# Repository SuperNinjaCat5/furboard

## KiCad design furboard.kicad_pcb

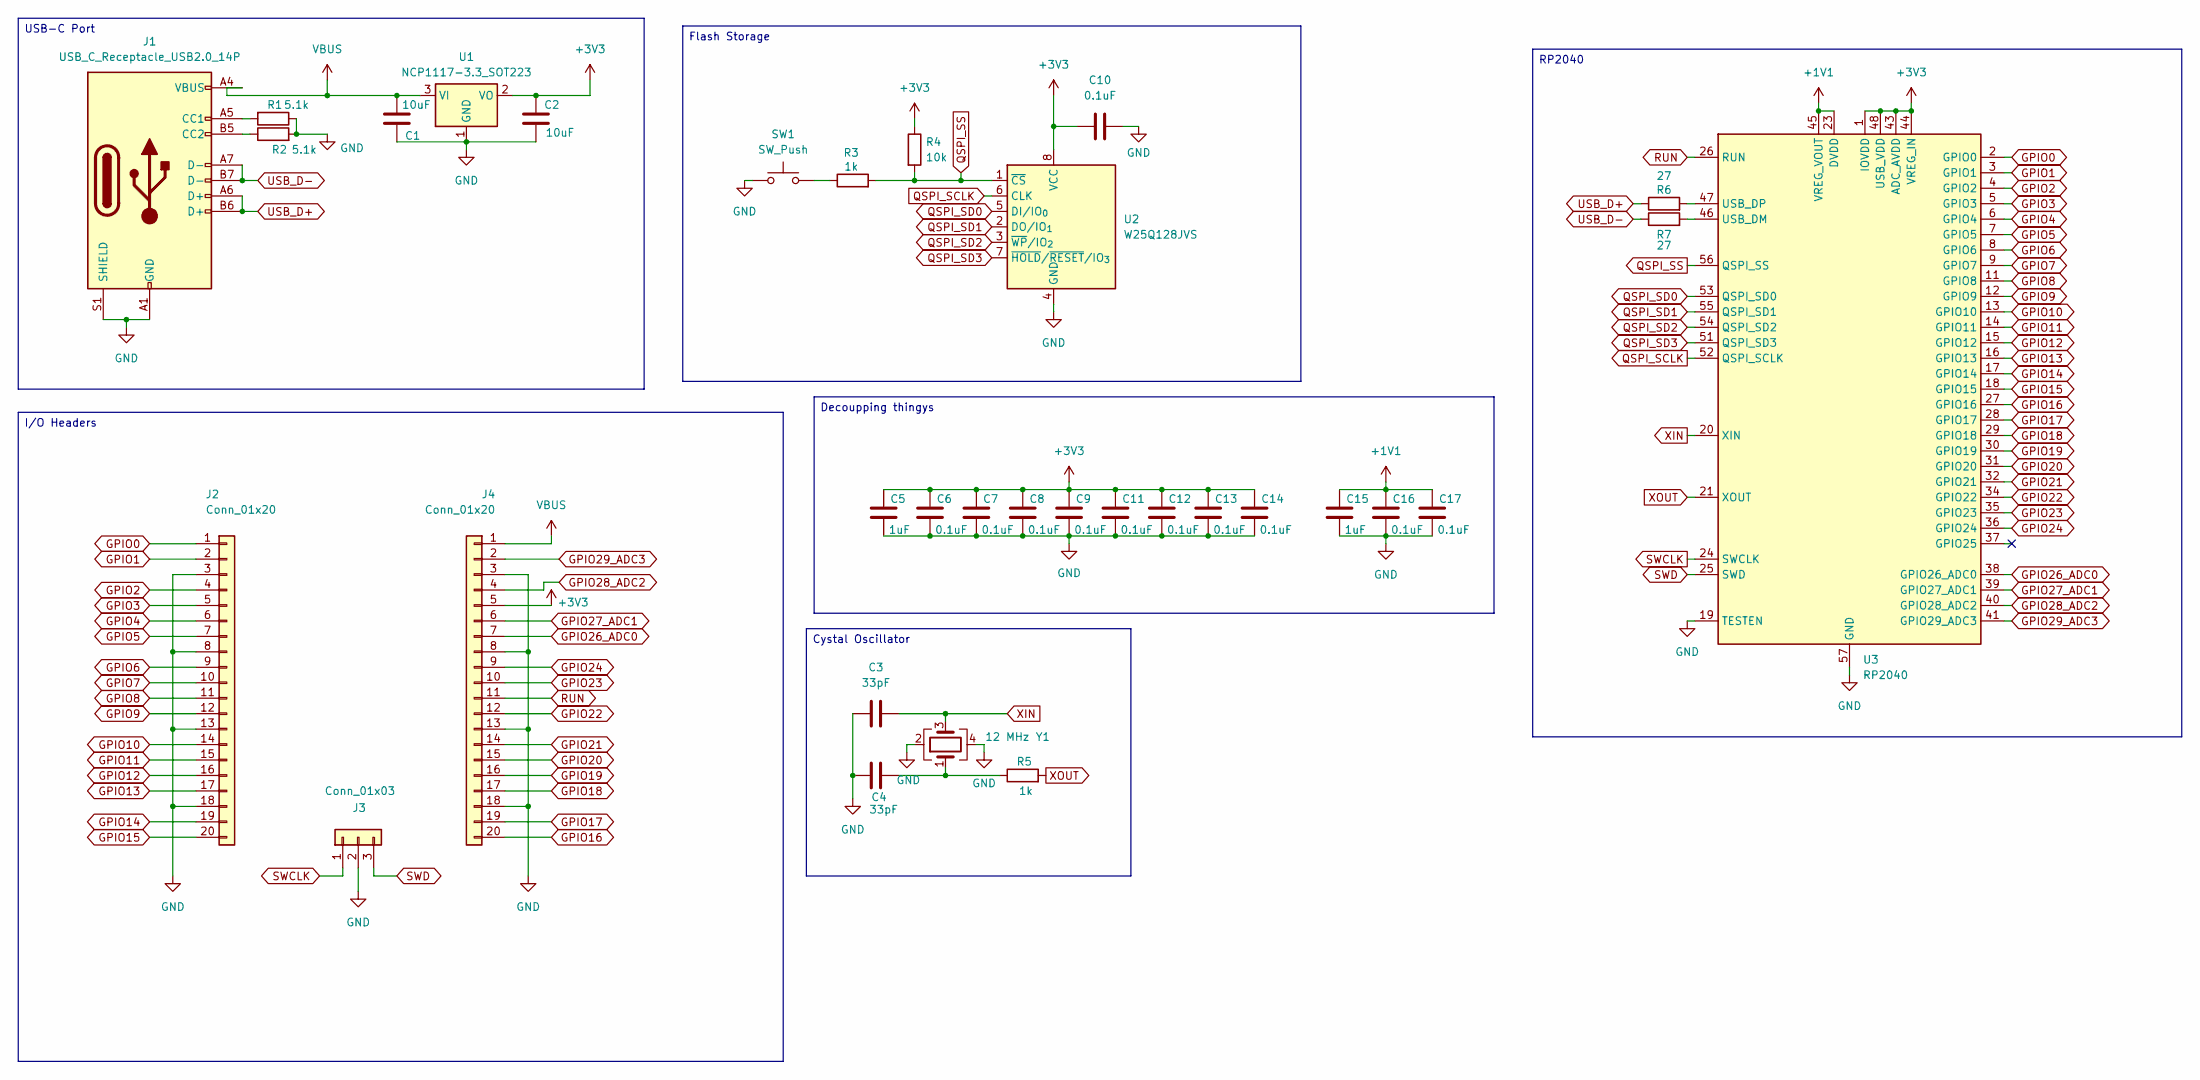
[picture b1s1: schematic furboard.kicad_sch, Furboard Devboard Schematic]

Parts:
C1, C2: 10uF; C_0201_0603Metric
C3, C4: 33pF; C_0402_1005Metric
C5, C15: 1uF; C_0402_1005Metric
C6, C7, C8, C9, C10, C11, C12, C13, C14, C16, C17: 0.1uF; C_0402_1005Metric
J1: USB_C_Receptacle_USB2.0_14P; USB_C_Receptacle_HRO_TYPE-C-31-M-12
J2, J4: Conn_01x20; PinHeader_1x20_P2.54mm_Vertical
J3: Conn_01x03; PinHeader_1x03_P2.54mm_Vertical
R1, R2: 5.1k; R_0402_1005Metric
R3, R5: 1k; R_0402_1005Metric
R4: 10k; R_0402_1005Metric
R6, R7: 27; R_0402_1005Metric
SW1: SW_Push; SW_Push_SPST_NO_Alps_SKRK
U1: NCP1117-3.3_SOT223; SOT-223-3_TabPin2
U2: W25Q128JVS; SOIC-8_5.3x5.3mm_P1.27mm
U3: RP2040; QFN-56-1EP_7x7mm_P0.4mm_EP3.2x3.2mm
Y1: 12 MHz; Crystal_SMD_3225-4Pin_3.2x2.5mm

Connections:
+1V1: C15.1, C16.1, C17.1, U3.23 (DVDD), U3.45 (VREG_VOUT), U3.50 (DVDD)
+3V3: C2.1, C5.1, C6.1, C7.1, C8.1, C9.1, C10.1, C11.1, C12.1, C13.1, C14.1, J4.5, R4.1, U1.2 (VO), U2.8 (VCC), U3.1 (IOVDD), U3.10 (IOVDD), U3.22 (IOVDD), U3.33 (IOVDD), U3.42 (IOVDD), U3.43 (ADC_AVDD), U3.44 (VREG_IN), U3.48 (USB_VDD), U3.49 (IOVDD)
GND: C1.2, C2.2, C3.1, C4.1, C5.2, C6.2, C7.2, C8.2, C9.2, C10.2, C11.2, C12.2, C13.2, C14.2, C15.2, C16.2, C17.2, J1.A1 (GND), J1.A12 (GND), J1.B1 (GND), J1.B12 (GND), J1.S1 (SHIELD), J2.3, J2.8, J2.13, J2.18, J3.2, J4.3, J4.8, J4.13, J4.18, R1.1, R2.2, SW1.1, U1.1 (GND), U2.4 (GND), U3.19 (TESTEN), U3.57 (GND), Y1.2, Y1.4
GPIO0: J2.1, U3.2 (GPIO0)
GPIO1: J2.2, U3.3 (GPIO1)
GPIO2: J2.4, U3.4 (GPIO2)
GPIO3: J2.5, U3.5 (GPIO3)
GPIO4: J2.6, U3.6 (GPIO4)
GPIO5: J2.7, U3.7 (GPIO5)
GPIO6: J2.9, U3.8 (GPIO6)
GPIO7: J2.10, U3.9 (GPIO7)
GPIO8: J2.11, U3.11 (GPIO8)
GPIO9: J2.12, U3.12 (GPIO9)
GPIO10: J2.14, U3.13 (GPIO10)
GPIO11: J2.15, U3.14 (GPIO11)
GPIO12: J2.16, U3.15 (GPIO12)
GPIO13: J2.17, U3.16 (GPIO13)
GPIO14: J2.19, U3.17 (GPIO14)
GPIO15: J2.20, U3.18 (GPIO15)
GPIO16: J4.20, U3.27 (GPIO16)
GPIO17: J4.19, U3.28 (GPIO17)
GPIO18: J4.17, U3.29 (GPIO18)
GPIO19: J4.16, U3.30 (GPIO19)
GPIO20: J4.15, U3.31 (GPIO20)
GPIO21: J4.14, U3.32 (GPIO21)
GPIO22: J4.12, U3.34 (GPIO22)
GPIO23: J4.10, U3.35 (GPIO23)
GPIO24: J4.9, U3.36 (GPIO24)
GPIO26_ADC0: J4.7, U3.38 (GPIO26_ADC0)
GPIO27_ADC1: J4.6, U3.39 (GPIO27_ADC1)
GPIO28_ADC2: J4.4, U3.40 (GPIO28_ADC2)
GPIO29_ADC3: J4.2, U3.41 (GPIO29_ADC3)
unnamed: C4.2, R5.1, Y1.1
unnamed: J1.A5 (CC1), R1.2
unnamed: J1.B5 (CC2), R2.1
unnamed: R3.1, SW1.2
unnamed: R7.2, U3.46 (USB_DM)
unnamed: R6.2, U3.47 (USB_DP)
QSPI_SCLK: U2.6 (CLK), U3.52 (QSPI_SCLK)
QSPI_SD0: U2.5 (DI/IO_{0}), U3.53 (QSPI_SD0)
QSPI_SD1: U2.2 (DO/IO_{1}), U3.55 (QSPI_SD1)
QSPI_SD2: U2.3 (~WP/IO_{2}), U3.54 (QSPI_SD2)
QSPI_SD3: U2.7 (~HOLD/~RESET/IO_{3}), U3.51 (QSPI_SD3)
QSPI_SS: R3.2, R4.2, U2.1 (~CS), U3.56 (QSPI_SS)
RUN: J4.11, U3.26 (RUN)
SWCLK: J3.1, U3.24 (SWCLK)
SWD: J3.3, U3.25 (SWD)
USB_D+: J1.A6 (D+), J1.B6 (D+), R6.1
USB_D-: J1.A7 (D-), J1.B7 (D-), R7.1
VBUS: C1.1, J1.A4 (VBUS), J1.A9 (VBUS), J1.B4 (VBUS), J1.B9 (VBUS), J4.1, U1.3 (VI)
XIN: C3.2, U3.20 (XIN), Y1.3
XOUT: R5.2, U3.21 (XOUT)

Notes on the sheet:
RP2040
USB-C Port
Cystal Oscillator
Decoupping thingys
I/O Headers
Flash Storage

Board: 2 copper layers, 33 parts (0 on the bottom side), 52 nets, no tracks yet.

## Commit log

2025-10-06 Add schematic and other project files
2025-10-06 Change caps to look nice
2025-10-07 Update the sch to be more organized, also started adding flash storage
2025-10-09 Fix the schematic to look nicer, add the cool text box thingys (w commit msg)
2025-10-09 Update the schematic data sheet thing
2025-10-12 Finish schematic draft, add pinout
2025-10-12 Use auto-anotate to fix my issues
2025-10-12 Test schematic with ERC and other tools to make minor adjustments
2025-10-12 Update schematic list of parts (footprint)
2025-10-12 Start working on the PCB, add shape, pins, and RP2040
